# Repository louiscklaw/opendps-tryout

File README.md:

### Power supply

link to documentation page:
[https://louiscklaw.github.io/opendps-tryout/](https://louiscklaw.github.io/opendps-tryout/)

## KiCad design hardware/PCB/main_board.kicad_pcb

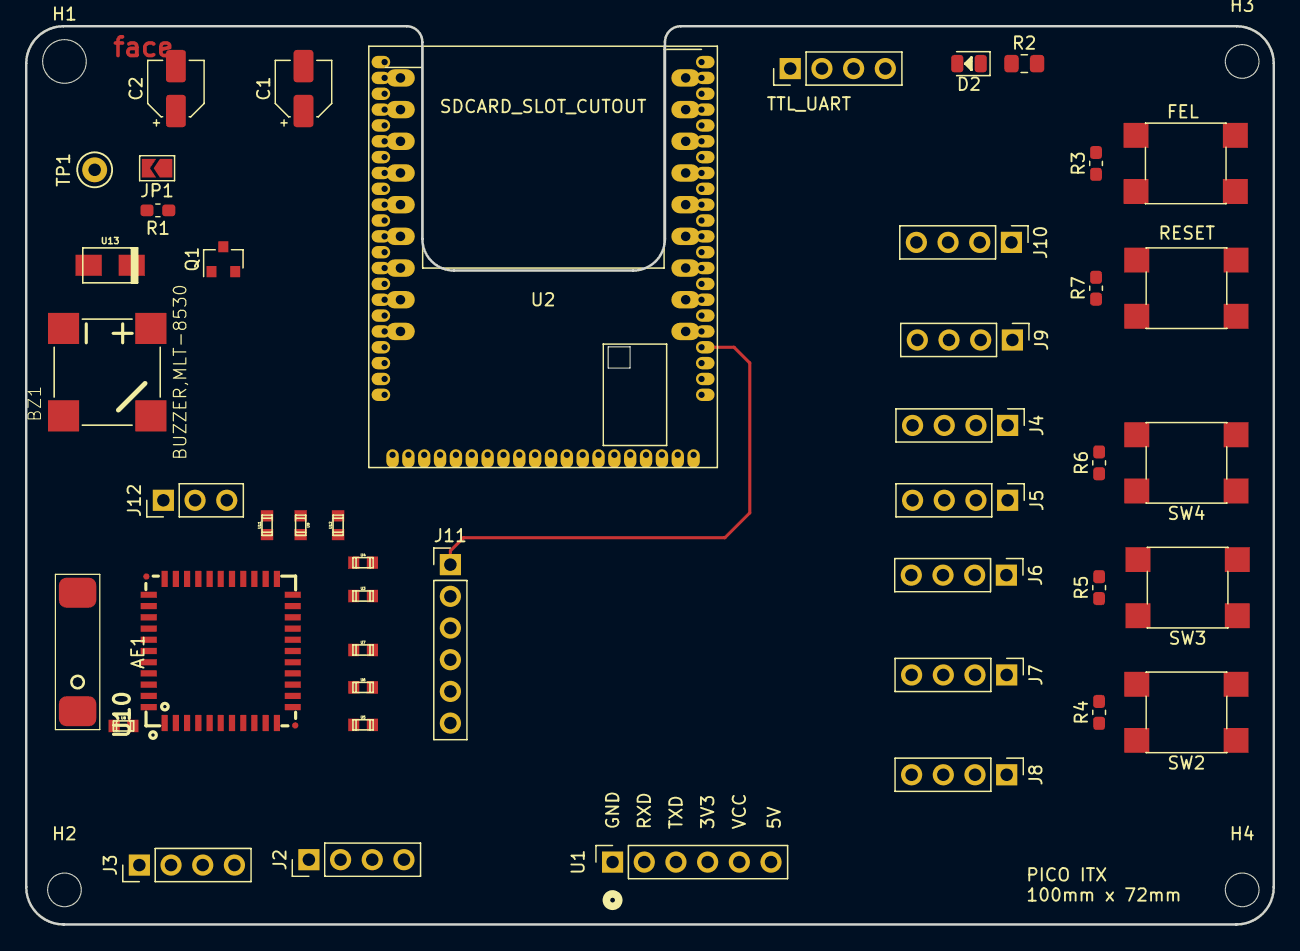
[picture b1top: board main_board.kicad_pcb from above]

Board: 2 copper layers, 100.0 x 72.0 mm, 49 parts (0 on the bottom side), 47 nets.

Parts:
AE1: Antenna_Shield; rainsun-AN9520
BZ1: BUZZER,MLT-8530; MLT-8530
C1, C2: CP47uf,10V; CP_Elec_4x5.3
D2: LED_GREEN,0805; LED_0805_2012Metric
H1, H2, H3, H4: MOUNT_M3; MountingHole_3.5mm_M3,rpi_like
J1: TTL_UART; PinHeader_1x04_P2.54mm_Vertical
J2: DPS1_UART; PinHeader_1x04_P2.54mm_Vertical
J3: DPS2_UART; PinHeader_1x04_P2.54mm_Vertical
J4: PE_IO_0; PinHeader_1x04_P2.54mm_Vertical
J5: PE_IO_1; PinHeader_1x04_P2.54mm_Vertical
J6: PE_IO_2; PinHeader_1x04_P2.54mm_Vertical
J7: PE_IO_3/TWI0; PinHeader_1x04_P2.54mm_Vertical
J8: PA_IO; PinHeader_1x04_P2.54mm_Vertical
J9: USB_IO; PinHeader_1x04_P2.54mm_Vertical
J10: POWER; PinHeader_1x04_P2.54mm_Vertical
J11: SDC_DEBUG; PinHeader_1x06_P2.54mm_Vertical
J12: UART_DEBUG; PinHeader_1x03_P2.54mm_Vertical
JP1: Jumper; SolderJumper-2_P1.3mm_Open_TrianglePad1.0x1.5mm
Q1: 2N3904(1AM); MBT3904_1AM_SOT
R1: R470,0603; R_0603_1608Metric_Pad1.05x0.95mm_HandSolder
R2: R103,0805; R_0805_2012Metric_Pad1.15x1.40mm_HandSolder
R3, R4, R5, R6, R7: R103,0603; R_0603_1608Metric_Pad1.05x0.95mm_HandSolder
SW1: FEL; SW_SPST_PTS645
SW2, SW3, SW4: SW_Push; SW_SPST_PTS645
SW5: RESET; SW_SPST_PTS645
TP1: TestPoint; TestPoint_Keystone_5000-5004_Miniature
U1: TTL_USB_CONVERTER
U2: LICHEEPI_NANO; licheepi_nano
U3, U4, U5, U6, U7: 47KΩ,(4702),±1%,0603,C25819; r_0603
U8: 33pF,(330),±5%,50V,C0G,0603,C1663; c_0603
U9, U11: 100KΩ,(1003),±1%,0603,C25803; r_0603
U10: RTL8723BS; RL-SM02BD(RTL8723BS)
U12: 10KΩ,(1002),±1%,0603,C25804; r_0603
U13: M1,GPP,SMA,DO-214AC,C123825; DO-214AC

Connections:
+3V3: J10.3, U2.12, U3.2, U4.2, U5.2, U6.2, U7.2, U9.2, U10.9, U10.22, U11.1, U12.1
+5V: BZ1.P, C1.1, C2.1, D2.2, J9.4, J10.2, SW5.2, U1.1, U2.8, U13.1
/I2C0-SCK: J7.1, U2.47
/I2C0-SDA: J7.2, U2.45
/PA0: J8.1, U2.14
/PA1: J8.2, U2.16
/PA2: J2.3, J8.3, U2.18
/PA3: J2.2, J8.4, U2.20
/PE2: J4.3, SW2.1, U2.2
/PE3: J4.4, SW3.1, U2.63
/PE4: J5.1, SW4.1, U2.61
/PE5: J5.2, U2.59
/PE6: J5.3, U2.57
/PE7: J3.2, J5.4, U2.55
/PE8: J3.3, J6.1, U2.53
/PE9: J6.2, JP1.1, U2.51
/PE10: J6.3, U2.49
/PI_TTL_RXD: J1.3, U1.5, U2.6
/PI_TTL_TXD: J1.2, U1.4, U2.4
/SDC1_CLK: J11.3, U2.50, U10.17
/SDC1_CMD: J11.4, U2.52, U7.1, U10.16
/SDC1_D0: J11.2, U2.48, U3.1, U10.18
/SDC1_D1: J11.1, U2.46, U4.1, U10.19
/SDC1_D2: J11.6, U2.56, U5.1, U10.14
/SDC1_D3: J11.5, U2.54, U6.1, U10.15
/USB_DM: J9.2, U2.1
/USB_DP: J9.3, U2.3
/gpio/FEL: SW1.1, U2.58
GND: C1.2, C2.2, J1.1, J2.1, J3.1, J9.1, J10.1, Q1.2, R2.2, R3.2, R4.2, R5.2, R6.2, R7.2, U1.6, U2.10, U10.1, U10.3, U10.20, U10.31, U10.33, U10.36, U10.41
unnamed: AE1.1, U8.2
unnamed: BZ1.N, Q1.3, U13.2
unnamed: D2.1, R2.1
unnamed: J12.1, U10.42
unnamed: J12.2, U10.43
unnamed: J12.3, U10.44
unnamed: JP1.2, R1.2, TP1.1
unnamed: Q1.1, R1.1
unnamed: R3.1, SW1.2
unnamed: R4.1, SW2.2
unnamed: R5.1, SW3.2
unnamed: R6.1, SW4.2
unnamed: R7.1, SW5.1
unnamed: U1.2, U1.3
unnamed: U8.1, U10.2
unnamed: U9.1, U10.12
unnamed: U10.23, U12.2
unnamed: U10.34, U11.2

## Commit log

2019-12-11 update,
2019-12-11 update github link,
2020-01-22 init commit for travis merge,
2020-01-22 init stl directory,
2020-01-22 fix for pipfile,
2020-01-22 init case-draft plan,
2020-01-22 update for draft case design screen capture,
2020-01-22 in the middle,
2020-01-26 update for freecad file,
2020-01-27 update model,
2020-01-27 update model screencapture
2020-01-27 update PCB stand
2020-01-27 update foot-stand
2020-01-28 update to fusion the case,
2020-01-28 update to pcb stand,
2020-02-02 update for right plate,
2020-02-03 update to re-model,
2020-02-03 update to save case_plan,
2020-02-03 update case design,
2020-02-03 update pcb stand,
2020-02-03 update for right-cover,
2020-02-03 update screw,
2020-02-03 before adding pov,
2020-02-03 update documentation,
2020-02-03 upadte parts dimensions picture,
2020-02-04 update file locations,
2020-02-04 init commit for mainboard pcb,
2020-02-04 update for pcb orientation, the screw hole should be fixed,
2020-02-04 update pcb screw hole position,
2020-02-08 update to mange using parts,
2020-03-05 update to merge after success,
2020-03-05 add project photo,
2020-03-07 update for datasheet pdf,
2020-03-10 init CAD files,
2020-03-13 update for atx power control,
2020-03-13 update for atx power control schematic,
2020-03-13 update references,
2020-03-17 add command excel table and ignore the temp ods file,
2020-03-23 update for workspace,
2020-04-03 update PCB,
2020-04-03 update for schematic,
2020-04-06 update requirements,
2020-04-16 update before change,
2020-04-16 update for adding usb ttl converter,
2020-04-17 sch: update buzzer connection,
2020-04-18 pcb: update for selective buzzer input,
2020-04-23 update new design,
2020-04-23 update and test new merger,
2020-04-23 add references,
2020-04-23 update design,
2020-04-25 update for io_bank,
2020-04-25 update rtl8723 circuit,
2020-04-25 update label,
2020-04-25 all components in the board,
2020-04-25 update tokens,
2020-04-27 update case,
2020-04-27 update for screw hole,
2020-04-27 update and test,
2020-04-29 update pcb mount,
2020-04-30 printing of case body, add 3mf file,
2020-04-30 fix printing orientation,
2020-04-30 init commit for credentials.yml and test,
2020-04-30 ci: update for freecad and stl testing,
2020-04-30 ci: fix wget command,
2020-04-30 ci: update for mkdir .travis directory,
2020-04-30 ci: init gitattributes and test,
2020-04-30 ci: update gitattributes,
2020-04-30 update for STEP file for gitattributes,
2020-05-15 ci: update travis credentials.yml,
2020-10-27 Bump cryptography from 2.8 to 3.2 in /_util
    Bumps [cryptography](https://github.com/pyca/cryptography) from 2.8 to 3.2.
    - [Release notes](https://github.com/pyca/cryptography/releases)
    - [Changelog](https://github.com/pyca/cryptography/blob/master/CHANGELOG.rst)
    - [Commits](https://github.com/pyca/cryptography/compare/2.8...3.2)
